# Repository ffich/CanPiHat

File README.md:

# 🐍🔌 CanPiHat — CAN Bus HAT for Raspberry Pi

A rugged **CAN-Bus HAT** for the **Raspberry Pi**, powered by the **Microchip MCP2515** CAN controller 🧠 and **MCP2551** high-speed transceiver. Perfect for automotive 🚗, industrial 🏭, and robotics 🤖 CAN applications.

---

## 📡 What is CAN Bus?

**CAN (Controller Area Network)** is a **robust, differential two-wire protocol** designed for reliable, real-time communication between multiple devices (ECUs).  

### ✨ Why CAN is Awesome:
- 🛡 **Reliable** — Automatic error detection, re-transmission & priority handling  
- 📏 **Efficient** — Reduces wiring complexity with a single shared bus  
- 🌍 **Versatile** — Used in cars 🚗, factories 🏭, robots 🤖, and building automation 🏢  

---

## 🛠 Features of CanPiHat

| Icon | Feature |
|------|---------|
| 🧠 | **MCP2515** — Stand-alone CAN 2.0B controller with SPI interface (up to 1 Mbps) |
| ⚡ | **MCP2551** — High-speed CAN transceiver for physical layer communication |
| 🍓 | **Pi HAT Form Factor** — Plugs directly into Raspberry Pi’s 40-pin header |
| 🔌 | **Plug & Play** — Just enable SPI and start sending/receiving CAN frames |

---

## 🚀 Why You’ll Love It

- 🛠 **Simple Setup** — Minimal wiring, quick configuration  
- 🎯 **Proven Hardware** — Trusted Microchip CAN ICs  
- 🔄 **Flexible Applications** — From OBD2 logging to factory automation  
- 📡 **SocketCAN Compatible** — Works with `can-utils` and Python CAN libraries  

---

## ⚙ Getting Started

1. 🍓 **Stack** the HAT onto your Raspberry Pi  
2. 🔌 **Connect** CAN_H & CAN_L to your network  
3. 🖥 **Enable** SPI via `raspi-config`  
4. 📦 **Install** can-utils:  
  `sudo apt install can-utils`
5. ⚡ Bring up the CAN interface:
  `sudo ip link set can0 up type can bitrate 500000`
7. 📡 Communicate:
  `cansend can0 123#DEADBEEF`
  `candump can0`

---

## 💡 Applications
Area	Examples
🚗 Automotive	OBD2 data logging, ECU communication
🏭 Industrial	Motor drives, PLC networking
🤖 Robotics	Multi-node sensor & actuator control
🏢 Automation	Building CAN-based sensors & lighting

---

## 🏆 Summary
The 🐍🔌 CanPiHat turns your Raspberry Pi into a CAN bus powerhouse — ideal for diagnostics, data logging, and embedded networking.
With MCP2515 + MCP2551 under the hood, you get rock-solid performance in a compact, plug-and-play package.

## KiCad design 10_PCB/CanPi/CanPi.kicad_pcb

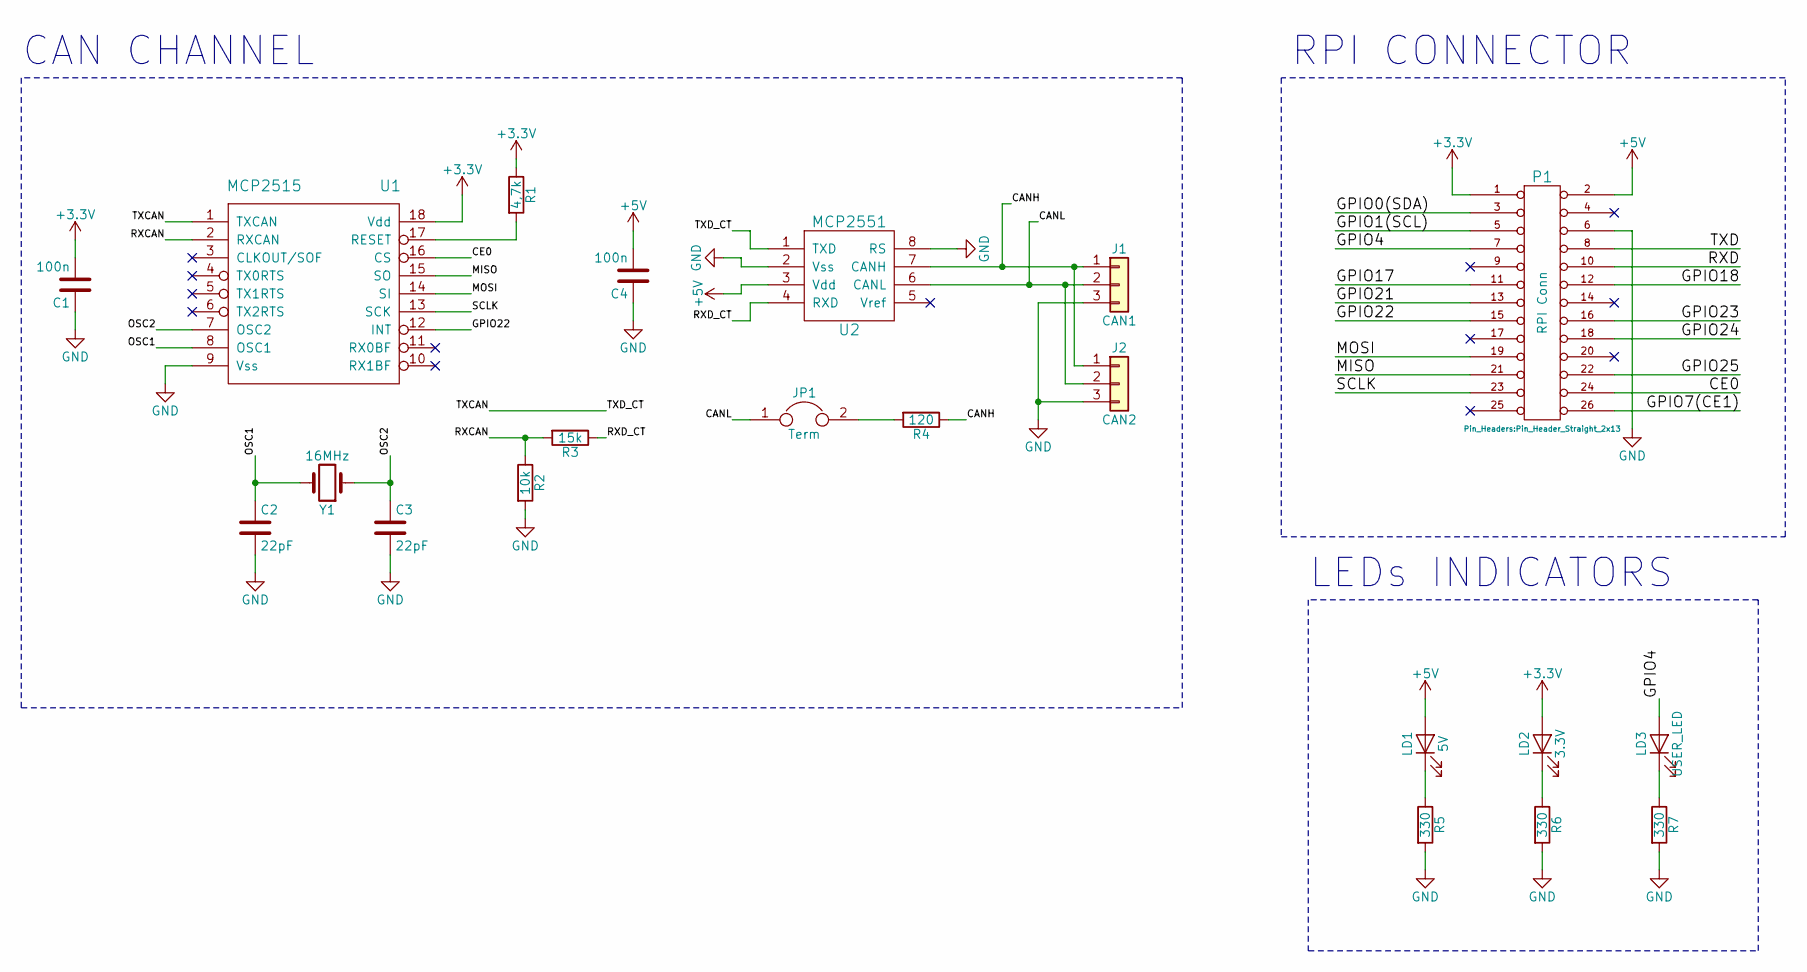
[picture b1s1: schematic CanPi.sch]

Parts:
C1, C4: 100n; c_0805
C2, C3: 22pF; c_0805
J1: CAN1; mkds_1,5-3
J2: CAN2; mkds_1,5-3
JP1: Term; pin_strip_2
LD1: 5V; Led_PLCC2_3528
LD2: 3.3V; Led_PLCC2_3528
LD3: USER_LED; Led_PLCC2_3528
P1: RPI Conn; Pin_Header_Straight_2x13
R1: 4,7k; r_0805
R2: 10k; r_0805
R3: 15k; r_0805
R4: 120; r_0805
R5, R6, R7: 330; r_0805
U1: MCP2515; soic-18
U2: MCP2551; so-8
Y1: 16MHz; crystal_hc-49%2fsmd

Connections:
+3V3: C1.2, LD2.2 (A), P1.1, R1.1, U1.18 (Vdd)
+5V: C4.2, LD1.2 (A), P1.2, U2.3 (Vdd)
/CANH: J1.1, J2.1, R4.1, U2.7 (CANH)
/CANL: J1.2, J2.2, JP1.1, U2.6 (CANL)
/CE0: P1.24 (P20), U1.16 (CS)
/GPIO0(SDA): P1.3
/GPIO1(SCL): P1.5
/GPIO4: LD3.2 (A), P1.7
/GPIO7(CE1): P1.26 (P22)
/GPIO17: P1.11
/GPIO18: P1.12
/GPIO21: P1.13
/GPIO22: P1.15, U1.12 (INT)
/GPIO23: P1.16
/GPIO24: P1.18
/GPIO25: P1.22
/MISO: P1.21, U1.15 (SO)
/MOSI: P1.19, U1.14 (SI)
/OSC1: C2.1, U1.8 (OSC1), Y1.2
/OSC2: C3.1, U1.7 (OSC2), Y1.1
/RXCAN: R2.1, R3.2, U1.2 (RXCAN)
/RXD: P1.10
/RXD_CT: R3.1, U2.4 (RXD)
/SCLK: P1.23, U1.13 (SCK)
/TXCAN: U1.1 (TXCAN), U2.1 (TXD)
/TXD: P1.8
GND: C1.1, C2.2, C3.2, C4.1, J1.3, J2.3, P1.6, R2.2, R5.2, R6.2, R7.2, U1.9 (Vss), U2.2 (Vss), U2.8 (RS)
unnamed: JP1.2, R4.2
unnamed: LD1.1 (K), R5.1
unnamed: LD2.1 (K), R6.1
unnamed: LD3.1 (K), R7.1
unnamed: R1.2, U1.17 (RESET)

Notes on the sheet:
RPI CONNECTOR
CAN CHANNEL
LEDs INDICATORS

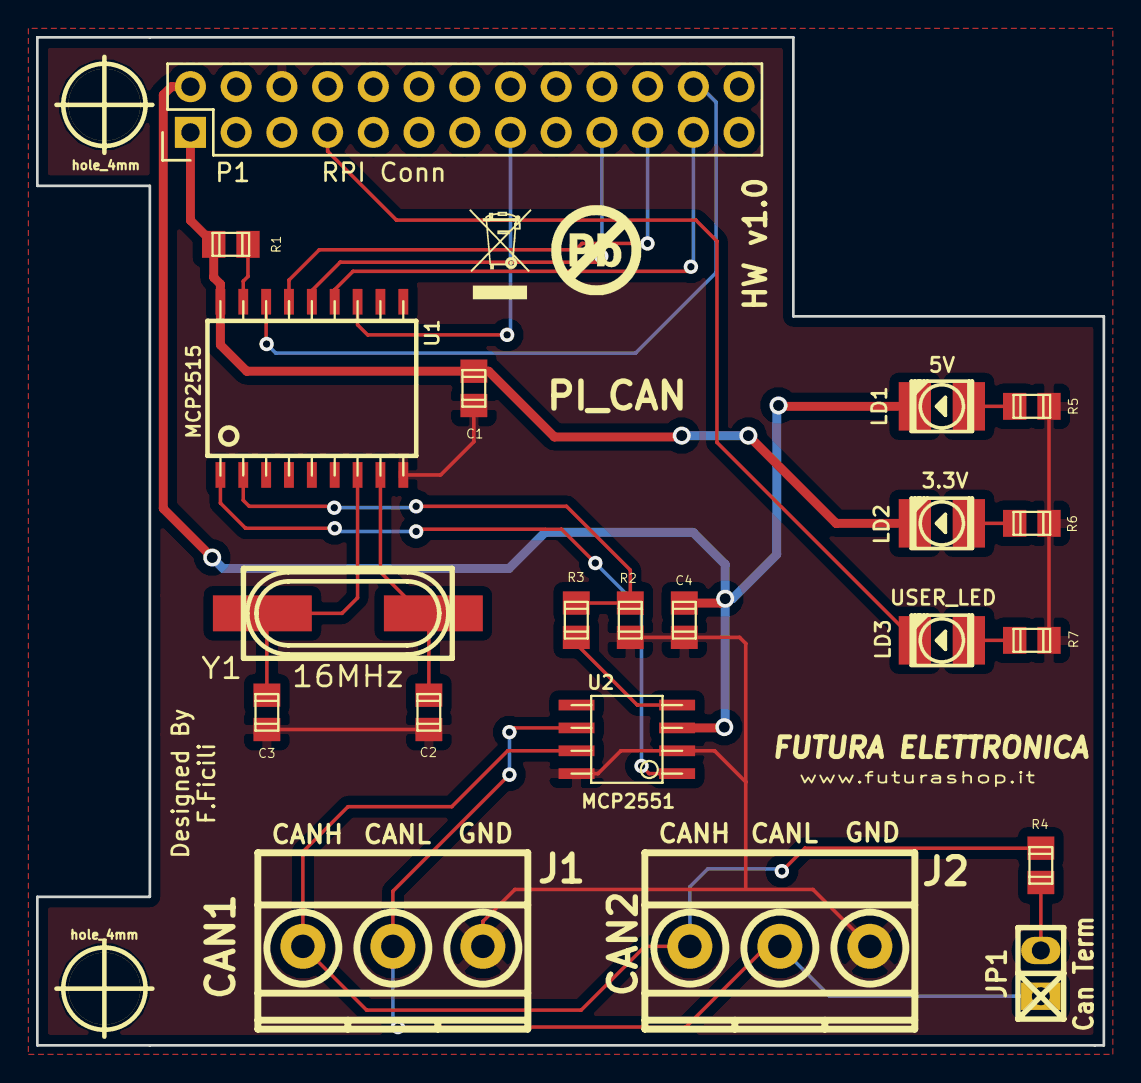
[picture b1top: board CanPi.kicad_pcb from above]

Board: 2 copper layers, 59.2 x 56.0 mm, 23 parts (0 on the bottom side), 21 nets.

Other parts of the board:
hole_4mm, hole_4mm#2: hole_4mm

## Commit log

2025-08-12 Update README.md
    added description
2025-08-12 Update README.md
    minor
